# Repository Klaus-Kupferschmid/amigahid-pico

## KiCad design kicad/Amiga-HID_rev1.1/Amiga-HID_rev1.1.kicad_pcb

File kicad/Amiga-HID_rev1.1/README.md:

# Amiga-HID rev1.1 — KiCad Project

> Stand-alone PCB design for the Amiga 2000 HID keyboard adapter.  
> RP235(0/4)A based, 20×55 mm, 4-layer PCB.

## Design Status: ✅ Complete

| Aspect | Status |
|--------|--------|
| Schematic | ✅ Complete (flat design) |
| PCB Layout | ✅ Complete |
| BOM | ✅ JLCPCB-ready |

---

## Bill of Materials (Stand: Mai 2026)

Kanonische BOM-Quelle: [`production/bom.csv`](production/bom.csv)

### MCU & Flash

| Ref | Value | LCSC | Footprint | Usage |
|-----|-------|------|-----------|-------|
| U4 | RP2354_60QFN | C41378174 | QFN-60 7×7mm | MCU (RP2350A mit internem 2MB Flash, alternativ RP2350A pinkompatibel) |
| U3 | W25Q16JVSSIQ | C82317 | SOIC-8 5.3×5.3mm | QSPI Flash 2 MB (DNP bei RP2354A) |
| Y1 | 12MHz | C3003246 | Crystal_SMD_3225 | Systemtakt (18 pF Load) |
| L1 | 3.3µH | C42411119 | L_pol_2016 | RP2350 SMPS-Induktivität (VREG_LX) |

### Power

| Ref | Value | LCSC | Footprint | Usage |
|-----|-------|------|-----------|-------|
| U2 | AMS1117-3.3 | C2688239 | SOT-223 | LDO 5V → 3.3V |
| D1, D2, D3 | PMEG2005AEA | C53114226 | SOD-323 | Power-OR Schottky-Dioden |
| F1 | 500mA | C7202014 | Fuse_1206 | PolyFuse Tastatur-VBUS |
| C1 | 10µF | C15850 | 0805 | VBUS Bulk-Cap |
| C3 | 22µF | C45783 | 0805 | LDO Output Bulk |

### USB & ESD

| Ref | Value | LCSC | Footprint | Usage |
|-----|-------|------|-----------|-------|
| J1 | USB-A | C42614 | USB_A_Edge | USB-A Buchse (Host/Flash) |
| U1 | USBLC6-2SC6 | C19170930 | SOT-23-6 | USB ESD-Schutz |
| R8, R9 | 27Ω | C25100 | 0402 | USB D+/D- Series-Termination |

### Level-Shifter (Amiga Interface)

| Ref | Value | LCSC | Footprint | Usage |
|-----|-------|------|-----------|-------|
| U5 | TXS0102DCUR | C53434 | VSSOP-8 | Bidir 3.3V↔5V für KB_DATA/KB_CLOCK |
| C22 | 100nF | C161530 | 0402 | TXS0102 VccA Decoupling (3V3) |
| C23 | 100nF | C161530 | 0402 | TXS0102 VccB Decoupling (5V) |

### Connectors

| Ref | Value | LCSC | Footprint | Usage |
|-----|-------|------|-----------|-------|
| J2 | JST S5B-XH-A | C42422447 | JST_XH_S5B-XH-A | Amiga / Front Panel (GND, 5V, KBDATA, NC, KBCLK) |
| J3 | Pin Header 1×04 | C52016392 | PinHeader_1x04_P2.54mm | SSD1309 OLED I2C (GND/VCC/SCL/SDA) |
| J4 | Pin Header 1×05 | C225480 | PinHeader_1x05_P2.54mm | Reserve (VSYS/GND/3V3/GP7/GP8) |
| J5 | JST-SH-3 | C160403 | JST_SH_SM03B-SRSS-TB | Pi Debug Probe SWD |
| J6 | JST-SH-3 | C160403 | JST_SH_SM03B-SRSS-TB | Pi Debug Probe UART |
| J7 | Conn_01x06 | C5372829 | PinHeader_1x06_P1.27mm | Zusatz-Reserve-Header |

### LEDs & Switches

| Ref | Value | LCSC | Footprint | Usage |
|-----|-------|------|-----------|-------|
| LED1 | Status_Green | C965804 | LED_0603 | Status/Power LED (GP25) |
| LED2 | Activity_Yellow | C72038 | LED_0603 | Activity LED (GP16) |
| R1, R2 | 1kΩ | C21190 | 0603 | LED-Vorwiderstände |
| SW1 | SW_Push | C139797 | SMD_Tact_4x3 | BOOTSEL Taster |
| SW2 | SW_Push | C139797 | SMD_Tact_4x3 | Reset Taster |

### Capacitors (Decoupling)

| Ref | Value | LCSC | Footprint | Usage |
|-----|-------|------|-----------|-------|
| C2, C4, C5 | 100nF | C1525 | 0402 | LDO Decoupling |
| C6, C7 | 15pF | C18164617 | 0402 | XTAL Load-Caps |
| C8, C9, C10, C12 | 4.7µF | C368809 | 0402 | MCU VREG/1V1 Decoupling |
| C11, C13–C21 | 100nF | C161530 | 0402 | MCU VDD / Flash Decoupling |
| C14 | 100nF | C161530 | 0402 | USB-VBUS Decoupling |

### Resistors

| Ref | Value | LCSC | Footprint | Usage |
|-----|-------|------|-----------|-------|
| R3 | 10kΩ | C25744 | 0402 | QSPI_SS Pullup |
| R4, R6, R7 | 1kΩ | C11702 | 0402 | Pullups |
| R5 | 33Ω | C25105 | 0402 | 3V3 RC-Filter (ADC_AVDD) |
| R10, R11 | 33Ω | C25105 | 0402 | UART TX/RX Series-Termination |
| R12, R13 | DNF | C25900 | 0402 | I2C Pullup-Pads (optional) |

### Misc

| Ref | Value | LCSC | Footprint | Usage |
|-----|-------|------|-----------|-------|
| SJ1 | OLED_VCC_SEL | – | SolderJumper-3 | OLED VCC: Default 3V3, optional 5V |

---

## Power Architecture

Passive dual-source switching (Amiga + PC USB):

```
   Amiga 5V (J2 Pin 2) ──►─D1──►─┬── Board-5V ──► AMS1117-3.3 ──► +3V3
                                 │
   USB-A VBUS (PC) ─────►─D2──►──┤
                                 │
                                 └─D3──►─F1──► USB-A VBUS (Tastatur)
```

✅ No FW logic required · ✅ Brick-resistant · ✅ Crash-safe

---

## GPIO Mapping (REV5)

| GPIO | Function | Connection |
|------|----------|------------|
| GP0 | UART_TX | J6 → Pi Debug Probe RX |
| GP1 | UART_RX | J6 ← Pi Debug Probe TX |
| GP2 | I2C1_SDA | OLED (J3 Pin 4) |
| GP3 | I2C1_SCL | OLED (J3 Pin 3) |
| GP5 | KB_DATA | → TXS0102 → J2 Pin 3 |
| GP6 | KB_CLOCK | → TXS0102 → J2 Pin 5 |
| GP7, GP8 | Reserve | J4 |
| GP16 | LED2 | Activity LED |
| GP25 | LED1 | Status LED |

---

## Tools

- **sync_lcsc_to_sch.py**: Synchronisiert LCSC-Nummern aus `production/bom.csv` in die Schematic

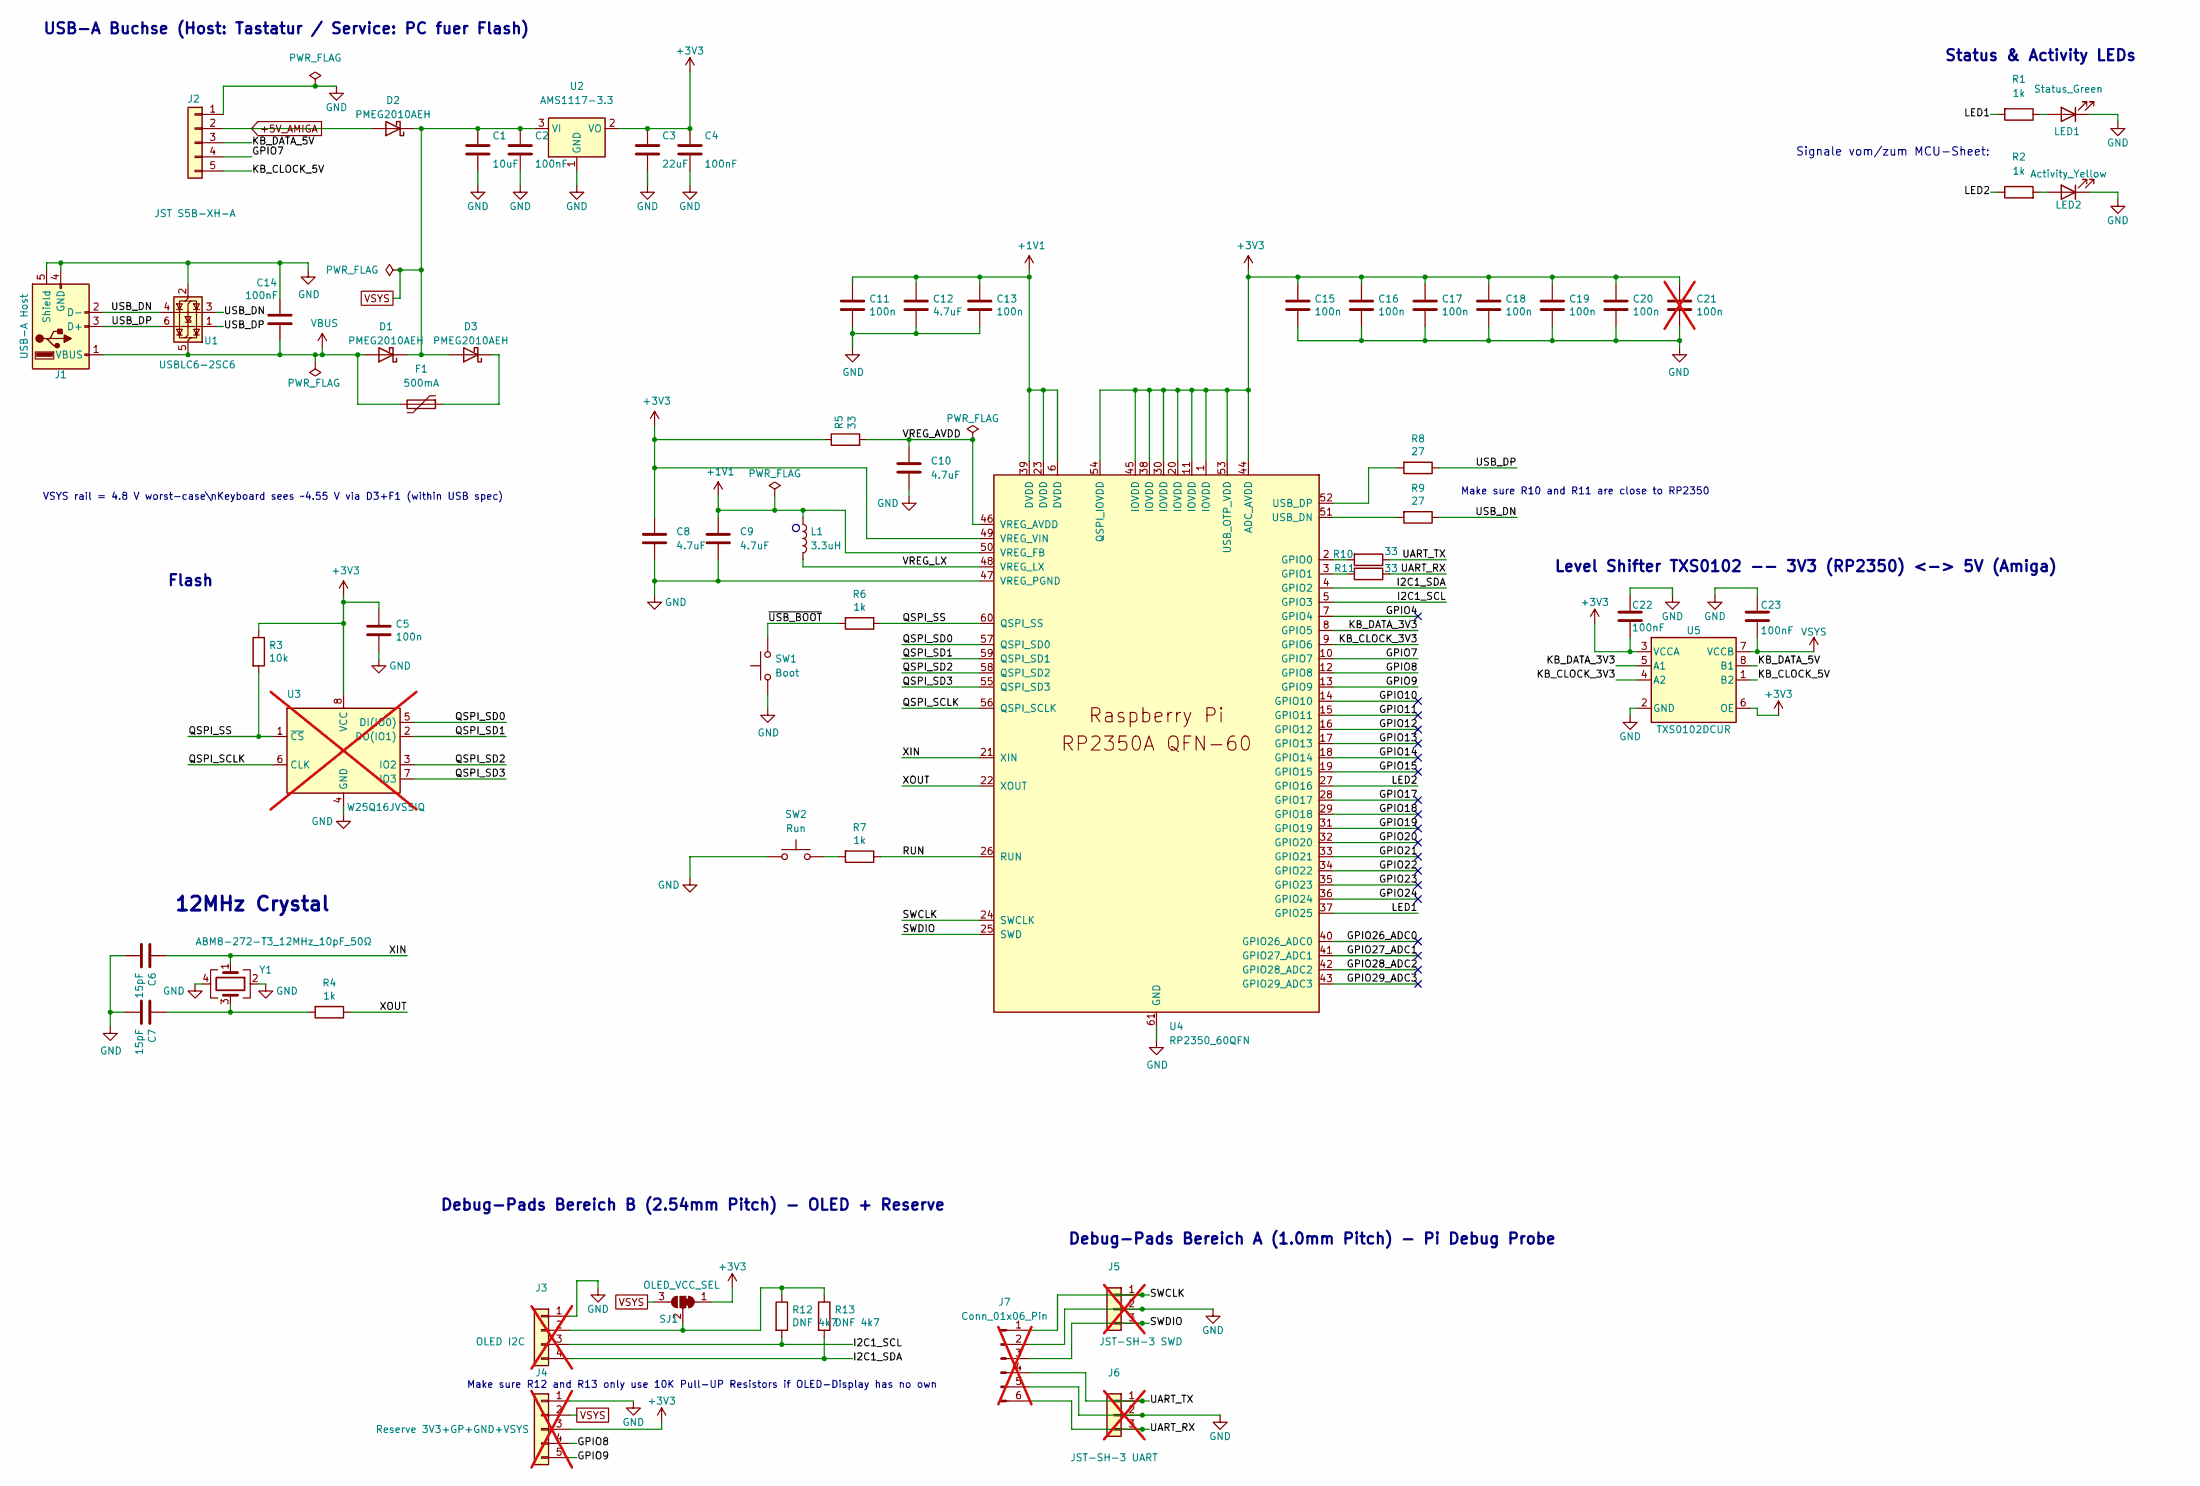
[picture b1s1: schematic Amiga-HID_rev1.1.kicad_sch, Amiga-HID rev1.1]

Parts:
C1: 10uF; C_0805_2012Metric; LCSC C15850
C2, C14, C22, C23: 100nF; C_0402_1005Metric; LCSC C161530
C3: 22uF; C_0805_2012Metric; LCSC C45783
C4: 100nF; C_0402_1005Metric; LCSC C1525
C5: 100n; C_0402_1005Metric; LCSC C1525
C6, C7: 15pF; C_0402_1005Metric; LCSC C18164617
C8, C9, C10, C12: 4.7uF; C_0402_1005Metric; LCSC C368809
C11, C13, C15, C16, C17, C18, C19, C20: 100n; C_0402_1005Metric; LCSC C161530
C21: 100n; C_0402_1005Metric; LCSC C161530; not fitted
D1, D2, D3: PMEG2010AEH; D_SOD-323; LCSC C53114226
F1: 500mA; Fuse_1206_3216Metric; LCSC C7202014
J1: USB-A Host; USB_A_Receptacle_Edge_C42614; LCSC C42614
J2: JST S5B-XH-A; S5B-XH-A; LCSC C42422447
J3: OLED I2C; PinHeader_1x04_P2.54mm_Vertical; LCSC C52016392; not fitted
J4: Reserve 3V3+GP+GND+VSYS; PinHeader_1x05_P2.54mm_Vertical; LCSC C225480; not fitted
J5: JST-SH-3 SWD; JST_SH_SM03B-SRSS-TB_1x03-1MP_P1.00mm_Horizontal; LCSC C160403; not fitted
J6: JST-SH-3 UART; JST_SH_SM03B-SRSS-TB_1x03-1MP_P1.00mm_Horizontal; LCSC C160403; not fitted
J7: Conn_01x06_Pin; PinHeader_1x06_P1.27mm_Vertical; LCSC C5372829; not fitted
L1: 3.3uH; L_pol_2016; MPN MWSA201610H2R2MT; LCSC C42411119
LED1: Status_Green; LED_0603_1608Metric; LCSC C965804
LED2: Activity_Yellow; LED_0603_1608Metric; LCSC C72038
R1, R2: 1k; R_0603_1608Metric; LCSC C21190
R3: 10k; R_0402_1005Metric; LCSC C25744
R4, R6, R7: 1k; R_0402_1005Metric; LCSC C11702
R5, R10, R11: 33; R_0402_1005Metric; LCSC C25105
R8, R9: 27; R_0402_1005Metric; LCSC C25100
R12, R13: DNF 4k7; R_0402_1005Metric; LCSC C25900
SJ1: OLED_VCC_SEL; SolderJumper-3_P1.3mm_Bridged12_RoundedPad1.0x1.5mm
SW1: Boot; SW_Push_1P1T_NO_Vertical_Wuerth_434133025816; LCSC C139797
SW2: Run; SW_Push_1P1T_NO_Vertical_Wuerth_434133025816; LCSC C139797
U1: USBLC6-2SC6; SOT-23-6; LCSC C19170930
U2: AMS1117-3.3; SOT-223-3_TabPin2; LCSC C2688239
U3: W25Q16JVSSIQ; SOIC-8_5.3x5.3mm_P1.27mm; LCSC C82317; not fitted
U4: RP2350_60QFN; RP2350-QFN-60-1EP_7x7_P0.4mm_EP3.4x3.4mm_ThermalVias; LCSC C41378174
U5: TXS0102DCUR; VSSOP-8_2.3x2mm_P0.5mm; LCSC C53434
Y1: ABM8-272-T3_12MHz_10pF_50Ω; Crystal_SMD_3225-4Pin_3.2x2.5mm; LCSC C20625731

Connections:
+1V1: C9.1, C11.1, C12.1, C13.1, L1.1, U4.6 (DVDD), U4.23 (DVDD), U4.39 (DVDD), U4.50 (VREG_FB)
+3V3: C3.1, C4.1, C5.1, C8.1, C15.1, C16.1, C17.1, C18.1, C19.1, C20.1, C21.1, C22.2, J4.3, R3.1, R5.1, SJ1.1 (A), U2.2 (VO), U3.8 (VCC), U4.1 (IOVDD), U4.11 (IOVDD), U4.20 (IOVDD), U4.30 (IOVDD), U4.38 (IOVDD), U4.44 (ADC_AVDD), U4.45 (IOVDD), U4.49 (VREG_VIN), U4.53 (USB_OTP_VDD), U4.54 (QSPI_IOVDD), U5.3 (VCCA), U5.6 (OE)
+5V_AMIGA: D2.2 (A), J2.2
/GPIO4: U4.7 (GPIO4)
/GPIO7: J2.4, U4.10 (GPIO7)
/GPIO8: J4.4, U4.12 (GPIO8)
/GPIO9: J4.5, U4.13 (GPIO9)
/GPIO10: U4.14 (GPIO10)
/GPIO11: U4.15 (GPIO11)
/GPIO12: U4.16 (GPIO12)
/GPIO13: U4.17 (GPIO13)
/GPIO14: U4.18 (GPIO14)
/GPIO15: U4.19 (GPIO15)
/GPIO17: U4.28 (GPIO17)
/GPIO18: U4.29 (GPIO18)
/GPIO19: U4.31 (GPIO19)
/GPIO20: U4.32 (GPIO20)
/GPIO21: U4.33 (GPIO21)
/GPIO22: U4.34 (GPIO22)
/GPIO23: U4.35 (GPIO23)
/GPIO24: U4.36 (GPIO24)
/GPIO26_ADC0: U4.40 (GPIO26_ADC0)
/GPIO27_ADC1: U4.41 (GPIO27_ADC1)
/GPIO28_ADC2: U4.42 (GPIO28_ADC2)
/GPIO29_ADC3: U4.43 (GPIO29_ADC3)
/I2C1_SCL: J3.3, R12.2, U4.5 (GPIO3)
/I2C1_SDA: J3.4, R13.2, U4.4 (GPIO2)
/KB_CLOCK_3V3: U4.9 (GPIO6), U5.4 (A2)
/KB_CLOCK_5V: J2.5, U5.1 (B2)
/KB_DATA_3V3: U4.8 (GPIO5), U5.5 (A1)
/KB_DATA_5V: J2.3, U5.8 (B1)
/LED1: R1.2, U4.37 (GPIO25)
/LED2: R2.1, U4.27 (GPIO16)
/QSPI_SCLK: U3.6 (CLK), U4.56 (QSPI_SCLK)
/QSPI_SD0: U3.5 (DI(IO0)), U4.57 (QSPI_SD0)
/QSPI_SD1: U3.2 (DO(IO1)), U4.59 (QSPI_SD1)
/QSPI_SD2: U3.3 (IO2), U4.58 (QSPI_SD2)
/QSPI_SD3: U3.7 (IO3), U4.55 (QSPI_SD3)
/QSPI_SS: R3.2, R6.1, U3.1 (~CS), U4.60 (QSPI_SS)
/RUN: R7.1, U4.26 (RUN)
/SWCLK: J5.1, J7.1, U4.24 (SWCLK)
/SWDIO: J5.3, J7.3, U4.25 (SWD)
/UART_RX: J6.3, J7.6, R11.1
/UART_TX: J6.1, J7.4, R10.1
/USB_DN: J1.2 (D-), R9.1, U1.3 (I/O2), U1.4 (I/O2)
/USB_DP: J1.3 (D+), R8.1, U1.1 (I/O1), U1.6 (I/O1)
/VREG_AVDD: C10.1, R5.2, U4.46 (VREG_AVDD)
/VREG_LX: L1.2, U4.48 (VREG_LX)
/XIN: C6.1, U4.21 (XIN), Y1.1
/XOUT: R4.1, U4.22 (XOUT)
/~USB_BOOT: R6.2, SW1.2
GND: C1.2, C2.2, C3.2, C4.2, C5.2, C6.2, C7.2, C8.2, C9.2, C10.2, C11.2, C12.2, C13.2, C14.1, C15.2, C16.2, C17.2, C18.2, C19.2, C20.2, C21.2, C22.1, C23.1, J1.4 (GND), J1.5 (Shield), J2.1, J3.1, J4.1, J5.2, J6.2, J7.2, J7.5, LED1.1 (K), LED2.1 (K), SW1.1, SW2.1, U1.2 (GND), U2.1 (GND), U3.4 (GND), U4.47 (VREG_PGND), U4.61 (GND), U5.2 (GND), Y1.2, Y1.4
unnamed: C7.1, R4.2, Y1.3
unnamed: D3.1 (K), F1.1
unnamed: J3.2, R12.1, R13.1, SJ1.2 (C)
unnamed: LED1.2 (A), R1.1
unnamed: LED2.2 (A), R2.2
unnamed: R7.2, SW2.2
unnamed: R10.2, U4.2 (GPIO0)
unnamed: R11.2, U4.3 (GPIO1)
unnamed: R9.2, U4.51 (USB_DN)
unnamed: R8.2, U4.52 (USB_DP)
VBUS: C14.2, D1.2 (A), F1.2, J1.1 (VBUS), U1.5 (VBUS)
VSYS: C1.1, C2.1, C23.2, D1.1 (K), D2.1 (K), D3.2 (A), J4.2, SJ1.3 (B), U2.3 (VI), U5.7 (VCCB)

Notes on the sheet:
USB-A Buchse (Host: Tastatur / Service: PC fuer Flash)
Make sure R12 and R13 only use 10K Pull-UP Resistors if OLED-Display has no own
Signale vom/zum MCU-Sheet:
Status & Activity LEDs
Flash
Debug-Pads Bereich B (2.54mm Pitch) - OLED + Reserve
Make sure R10 and R11 are close to RP2350
Level Shifter TXS0102 -- 3V3 (RP2350) <-> 5V (Amiga)
12MHz Crystal
VSYS rail = 4.8 V worst-case\nKeyboard sees ~4.55 V via D3+F1 (within USB spec)
Debug-Pads Bereich A (1.0mm Pitch) - Pi Debug Probe

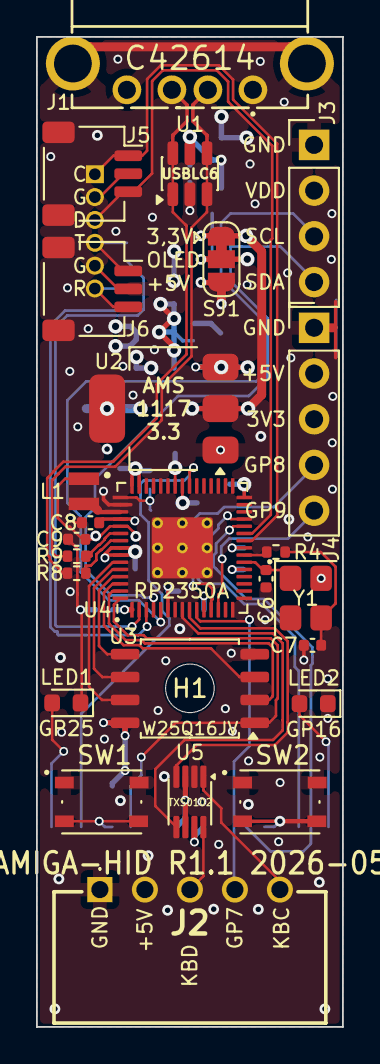
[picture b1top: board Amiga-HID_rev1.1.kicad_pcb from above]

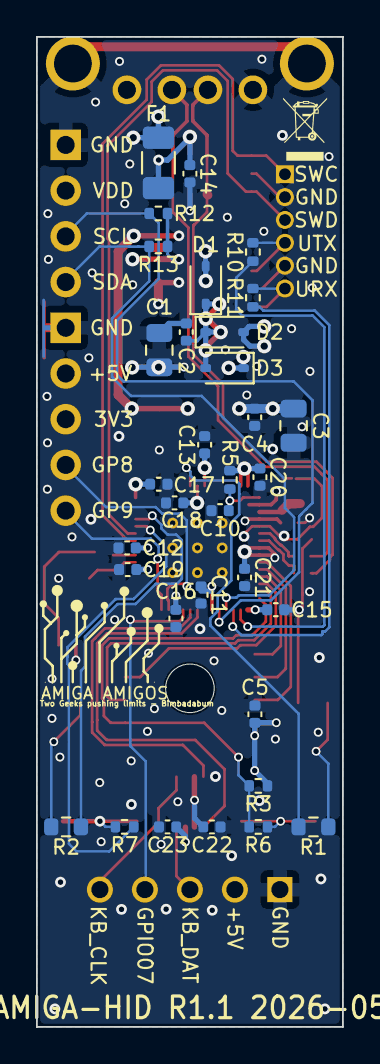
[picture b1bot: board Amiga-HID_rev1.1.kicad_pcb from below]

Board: 4 copper layers, 17.0 x 55.0 mm, 60 parts (33 on the bottom side), 45 nets.

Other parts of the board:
H1: MountingHole; MountingHole_2.7mm

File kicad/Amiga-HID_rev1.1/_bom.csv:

"Designator","Comment","Footprint","JLCPCB Part #","Usage"
"C1","10uF","Capacitor_SMD:C_0805_2012Metric","C15850","VBUS / Board-5V Bulk-Cap"
"C2","100nF","Capacitor_SMD:C_0402_1005Metric","C161530","LDO U2 IN-Decoupling"
"C3","22uF","Capacitor_SMD:C_0805_2012Metric","C45783","LDO U2 OUT Bulk (3V3)"
"C4","100nF","Capacitor_SMD:C_0402_1005Metric","C1525","LDO U2 OUT-Decoupling"
"C5","100nF","Capacitor_SMD:C_0402_1005Metric","C1525","Decoupling"
"C6","15pF","Capacitor_SMD:C_0402_1005Metric","C18164617","XTAL Y1 Load-Cap"
"C7","15pF","Capacitor_SMD:C_0402_1005Metric","C18164617","XTAL Y1 Load-Cap"
"C8","4.7uF","Capacitor_SMD:C_0402_1005Metric","C368809","MCU VREG_VIN Decoupling"
"C9","4.7uF","Capacitor_SMD:C_0402_1005Metric","C368809","MCU VREG SMPS-Cap"
"C10","4.7uF","Capacitor_SMD:C_0402_1005Metric","C368809","MCU 1V1 Bulk"
"C11","100nF","Capacitor_SMD:C_0402_1005Metric","C161530","3V3 RC-Filter mit R5 (ADC/USB_VDD)"
"C12","4.7uF","Capacitor_SMD:C_0402_1005Metric","C368809","MCU 1V1 Bulk"
"C13","100nF","Capacitor_SMD:C_0402_1005Metric","C161530","Decoupling"
"C14","100nF","Capacitor_SMD:C_0402_1005Metric","C161530","USB-VBUS Decoupling am Power-OR (USBLC6 / Schottky-Knoten)"
"C15","100nF","Capacitor_SMD:C_0402_1005Metric","C161530","MCU VDD Pin-Decoupling"
"C16","100nF","Capacitor_SMD:C_0402_1005Metric","C161530","MCU VDD Pin-Decoupling"
"C17","100nF","Capacitor_SMD:C_0402_1005Metric","C161530","MCU VDD Pin-Decoupling"
"C18","100nF","Capacitor_SMD:C_0402_1005Metric","C161530","MCU VDD Pin-Decoupling"
"C19","100nF","Capacitor_SMD:C_0402_1005Metric","C161530","MCU VDD Pin-Decoupling"
"C20","100nF","Capacitor_SMD:C_0402_1005Metric","C161530","MCU VDD Pin-Decoupling"
"C21","100nF","Capacitor_SMD:C_0402_1005Metric","C161530","U3 Flash VCC Decoupling (DNP bei RP2354A)"
"C22","100nF","Capacitor_SMD:C_0402_1005Metric","C161530","TXS0102 U5 Vcc-A Decoupling (3V3)"
"C23","100nF","Capacitor_SMD:C_0402_1005Metric","C161530","TXS0102 U5 Vcc-B Decoupling (5V)"
"D1","PMEG2005AEA 115-JSM","Diode_SMD:D_SOD-323","C53114226","Power-OR: Amiga 5V (J2 Pin2) -> Board-5V"
"D2","PMEG2005AEA 115-JSM","Diode_SMD:D_SOD-323","C53114226","Power-OR: USB-A VBUS (PC-Speisung) -> Board-5V"
"D3","PMEG2005AEA 115-JSM","Diode_SMD:D_SOD-323","C53114226","Power-OR: Board-5V -> USB-A VBUS (Tastatur-Speisung)"
"F1","500mA","Fuse:Fuse_1206_3216Metric","C7202014","PolyFuse Tastatur-VBUS (Kurzschluss-Schutz)"
"J1","USB-A Host","Amiga-HID_rev1.0:USB_A_Receptacle_Edge_C42614","C42614","USB-A Buchse (Tastatur-Host / PC-Flash via USB-A<->USB-A)"
"J2","JST-XH-5A","Connector_JST:JST_XH_B5B-XH-A_1x05_P2.50mm_Vertical","C7551124","Verbindung Amiga / Front Panel (GND, 5V, KBDATA, NC, KBCLK)"
"J3","OLED I2C","Connector_PinHeader_2.54mm:PinHeader_1x04_P2.54mm_Vertical","C52016392","SSD1309 OLED I2C (GND/VCC/SCL/SDA)"
"J4","Reserve 3V3+GP+GND+VSYS","Connector_PinHeader_2.54mm:PinHeader_1x05_P2.54mm_Vertical","C225480","Reserve 5-Pin (VSYS/GND/3V3/GP7/GP8)"
"J5","JST-SH-3 SWD","Connector_JST:JST_SH_SM03B-SRSS-TB_1x03-1MP_P1.00mm_Horizontal","C160403","Pi Debug Probe SWD (SWCLK/GND/SWDIO)"
"J6","JST-SH-3 UART","Connector_JST:JST_SH_SM03B-SRSS-TB_1x03-1MP_P1.00mm_Horizontal","C160403","Pi Debug Probe UART (TX/GND/RX)"
"J7","Conn_01x06_Pin","Connector_PinHeader_1.27mm:PinHeader_1x06_P1.27mm_Vertical","C5372829","Zusatz-Header (Reserve)"
"L1","3.3uH","Amiga-HID_rev1.0:L_pol_2016","C42411119","RP2350 SMPS-Induktivitaet (VREG_LX), Abracon AOTA-B201610S3R3 shielded power inductor"
"LED1","Status_Green","LED_SMD:LED_0603_1608Metric","C965804","Status/Power LED an GP25"
"LED2","Activity_Yellow","LED_SMD:LED_0603_1608Metric","C72038","Activity LED (USB-Traffic) an GP16"
"R1","330","Resistor_SMD:R_0603_1608Metric","C23138","LED1 Vorwiderstand (GP25 -> Status_Green)"
"R2","330","Resistor_SMD:R_0603_1608Metric","C23138","LED2 Vorwiderstand (GP16 -> Activity_Yellow)"
"R3","10k","Resistor_SMD:R_0402_1005Metric","C25744","QSPI_SS Pullup gegen +3V3 (Pico-2-Ref Pflicht)"
"R4","1k","Resistor_SMD:R_0402_1005Metric","C11702","Pullup / generischer Widerstand"
"R5","33","Resistor_SMD:R_0402_1005Metric","C25105","3V3 RC-Filter mit C11 (ADC_AVDD / USB_VDD33)"
"R6","1k","Resistor_SMD:R_0402_1005Metric","C11702","Pullup / generischer Widerstand"
"R7","1k","Resistor_SMD:R_0402_1005Metric","C11702","Pullup / generischer Widerstand"
"R8","27","Resistor_SMD:R_0402_1005Metric","C25100","USB D+ Series-Termination (USB-Spec 90 Ohm diff)"
"R9","27","Resistor_SMD:R_0402_1005Metric","C25100","USB D- Series-Termination (USB-Spec 90 Ohm diff)"
"R10","33","Resistor_SMD:R_0402_1005Metric","C25105","UART_TX Series-Termination MCU GP0 -> J6 Pin1"
"R11","33","Resistor_SMD:R_0402_1005Metric","C25105","UART_RX Series-Termination J6 Pin3 -> MCU GP1"
"R12","DNF","Resistor_SMD:R_0402_1005Metric","C25900","I2C1_SDA Pullup-Pad (DNF, OLED-Modul hat eigene Pullups; bei Bedarf 4k7)"
"R13","DNF","Resistor_SMD:R_0402_1005Metric","C25900","I2C1_SCL Pullup-Pad (DNF, OLED-Modul hat eigene Pullups; bei Bedarf 4k7)"
"SJ1","OLED_VCC_SEL","Jumper:SolderJumper-3_P1.3mm_Bridged12_RoundedPad1.0x1.5mm",,"Loetjumper OLED VCC: Default 3V3 (Pads 1+2 gebrueckt), alternativ auf 5V umloeten"
"SW1","SW_Push","Amiga-HID_rev1.0:SW_SMD_Tact_4x3_4P_C139797","C139797","BOOTSEL Hardware-Fallback Taster"
"SW2","SW_Push","Amiga-HID_rev1.0:SW_SMD_Tact_4x3_4P_C139797","C139797","Reset / User-Taster"
"U1","USBLC6-2SC6","Package_TO_SOT_SMD:SOT-23-6","C19170930","USB ESD-Schutz auf D+/D-"
"U2","AMS1117-3.3","Package_TO_SOT_SMD:SOT-223-3_TabPin2","C2688239","LDO 5V -> 3V3 (>=800 mA)"
"U3","W25Q16JVSSIQ","Amiga-HID_rev1.0:SOIC-8_5.3x5.3mm_P1.27mm","C82317","QSPI Flash 2 MB (DNP bei RP2354A flashless)"
"U4","RP2354_60QFN","Amiga-HID_rev1.0:RP2350-QFN-60-1EP_7x7_P0.4mm_EP3.4x3.4mm_ThermalVias","C41378174","MCU RP2350A (alternativ pinkompatibel RP2354A mit internem Stacked-Flash)"
"U5","TXS0102DCUR","Package_SO:VSSOP-8_2.3x2mm_P0.5mm","C53434","Bidir Level-Shifter 3V3<->5V fuer KB_DATA/KB_CLOCK"
"Y1","ABM8-272-T3_12MHz_10pF","Crystal:Crystal_SMD_3225-4Pin_3.2x2.5mm","C20625731","Systemtakt 12 MHz (Abracon ABM8-272-T3, Raspberry Pi zertifiziert)"

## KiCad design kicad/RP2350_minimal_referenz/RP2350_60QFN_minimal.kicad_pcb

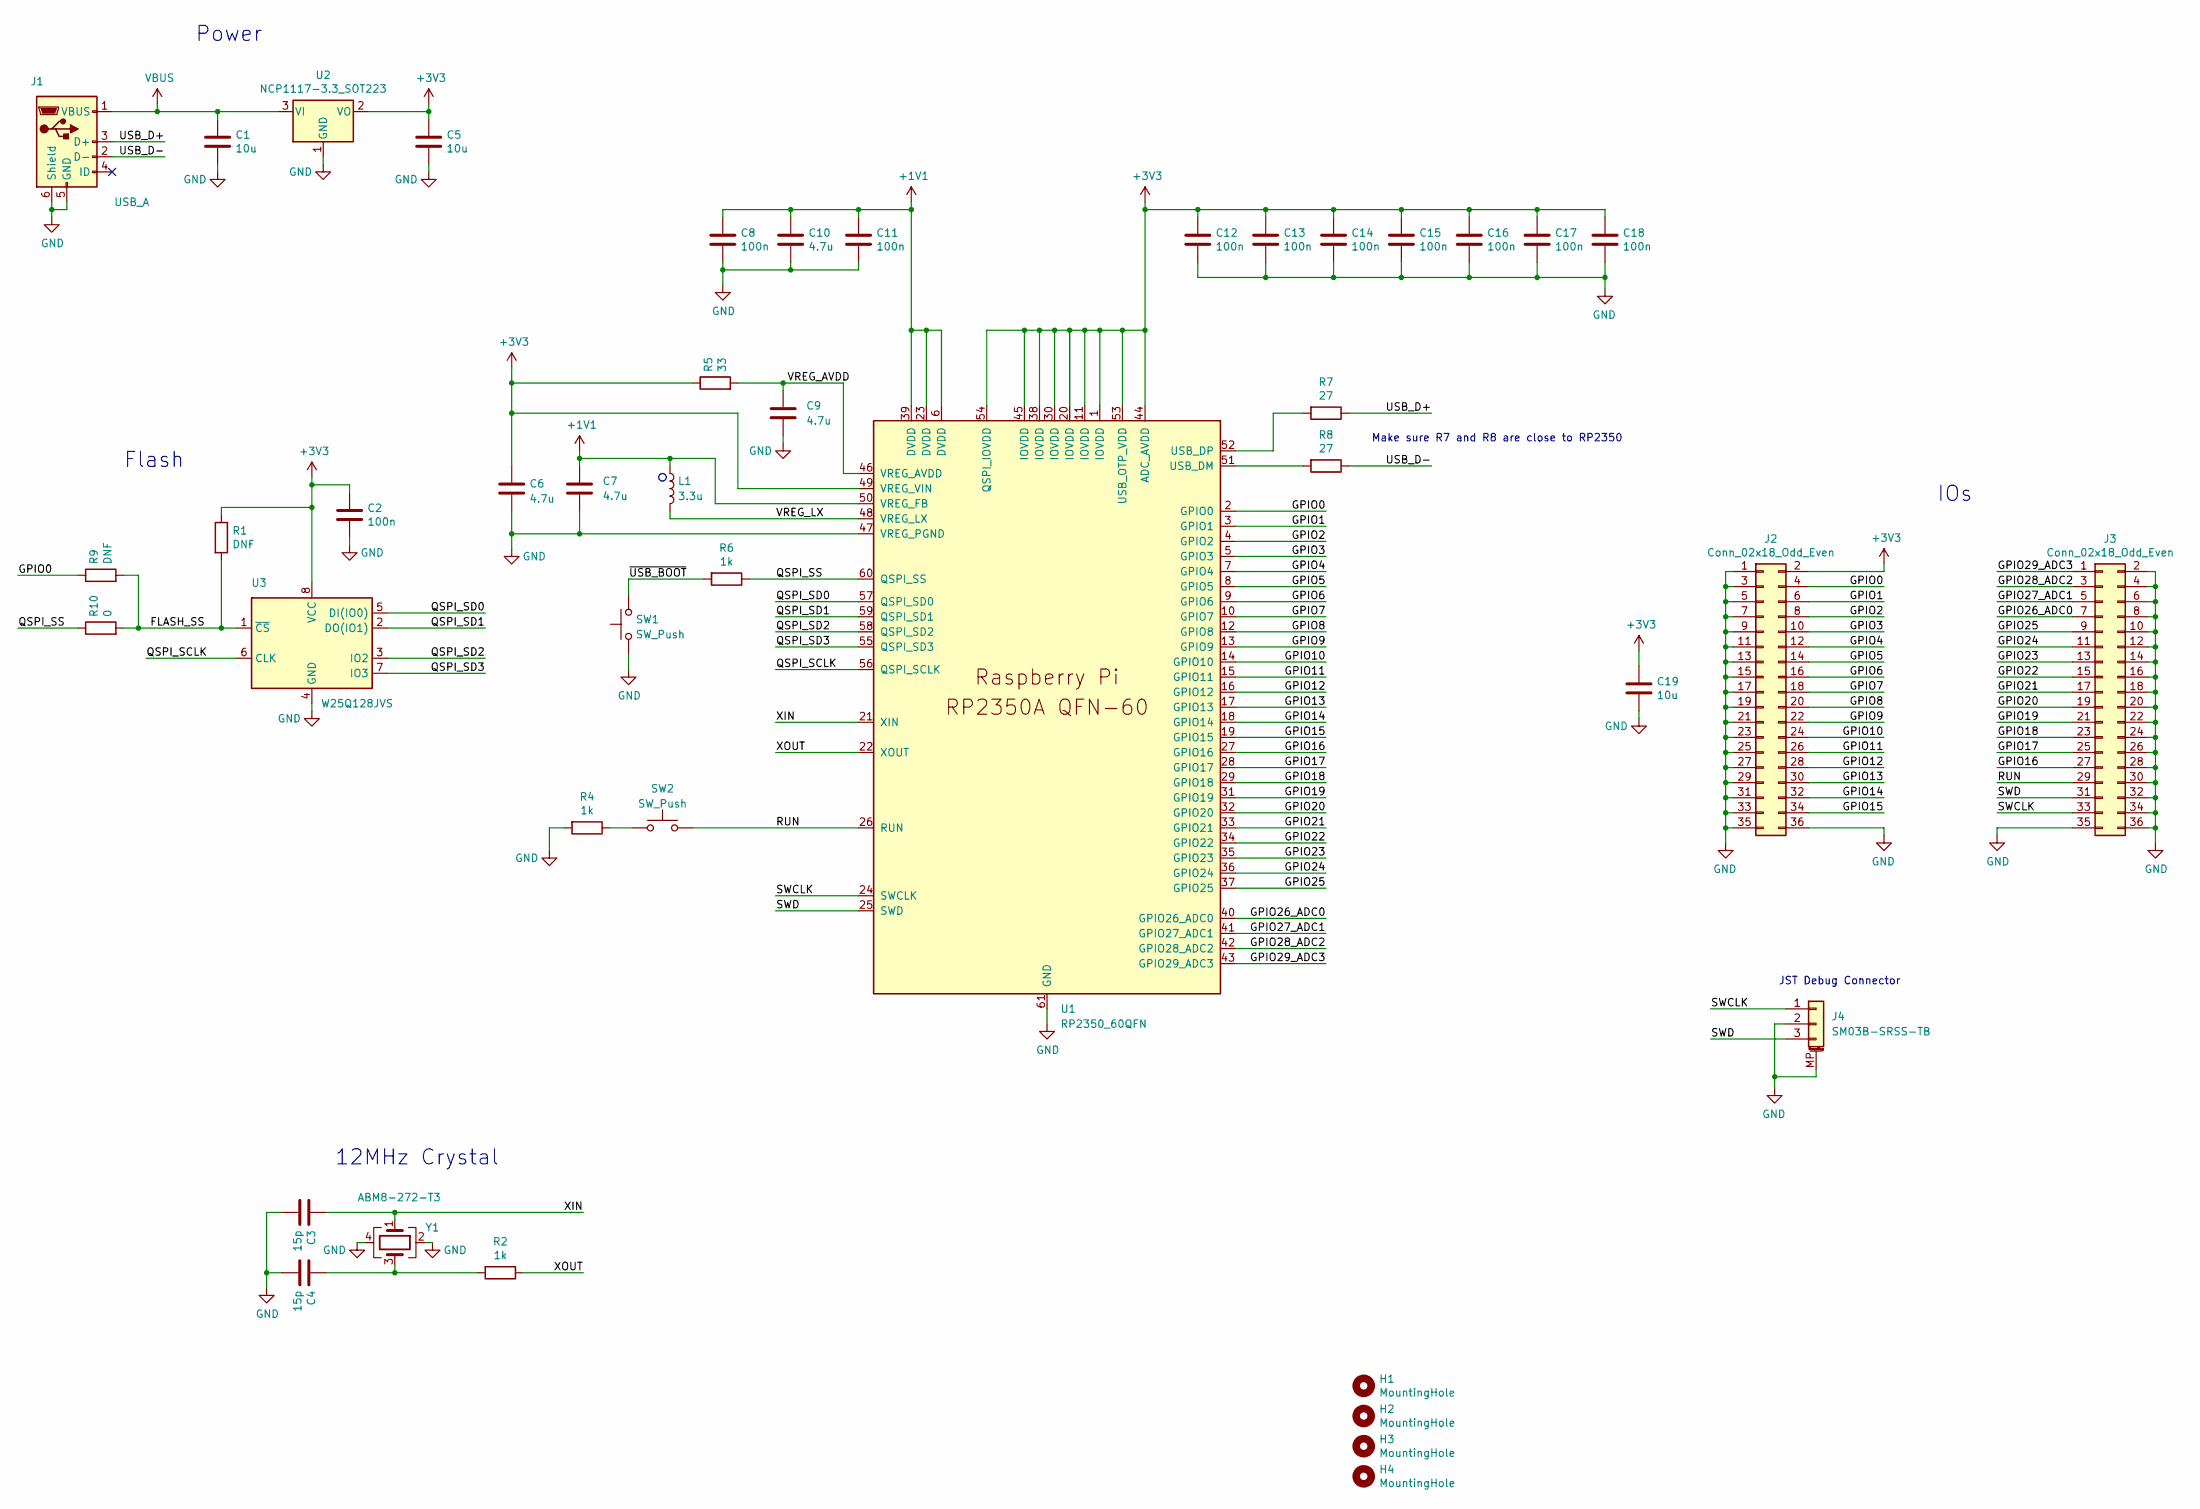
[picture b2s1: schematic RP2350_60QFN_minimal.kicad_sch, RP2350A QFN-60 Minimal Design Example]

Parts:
C1, C5, C19: 10u; C_0805_2012Metric
C2, C8, C11, C12, C13, C14, C15, C16, C17, C18: 100n; C_0402_1005Metric
C3, C4: 15p; C_0402_1005Metric
C6, C7: 4.7u; C_0402_1005Metric_small_pads
C9, C10: 4.7u; C_0402_1005Metric
H1, H2, H3, H4: MountingHole; MountingHole_2.7mm_M2.5
J1: USB_A; USB_Micro-B_Amphenol_10103594-0001LF_Horizontal
J2, J3: Conn_02x18_Odd_Even; PinHeader_2x18_P2.54mm_Vertical
J4: SM03B-SRSS-TB; JST_SH_SM03B-SRSS-TB_1x03-1MP_P1.00mm_Horizontal
L1: 3.3u; L_pol_2016
R1, R9: DNF; R_0402_1005Metric
R2, R4, R6: 1k; R_0402_1005Metric
R5: 33; R_0402_1005Metric
R7, R8: 27; R_0402_1005Metric
R10: 0; R_0402_1005Metric
SW1, SW2: SW_Push; SW_Push_1P1T_NO_Vertical_Wuerth_434133025816
U1: RP2350_60QFN; RP2350-QFN-60-1EP_7x7_P0.4mm_EP3.4x3.4mm_ThermalVias
U2: NCP1117-3.3_SOT223; SOT-223-3_TabPin2
U3: W25Q128JVS; SOIC-8_5.23x5.23mm_P1.27mm
Y1: ABM8-272-T3; Crystal_SMD_3225-4Pin_3.2x2.5mm

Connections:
+1V1: C7.1, C8.1, C10.1, C11.1, L1.1, U1.6 (DVDD), U1.23 (DVDD), U1.39 (DVDD), U1.50 (VREG_FB)
+3V3: C2.1, C5.1, C6.1, C12.1, C13.1, C14.1, C15.1, C16.1, C17.1, C18.1, C19.1, J2.2, R1.1, R5.1, U1.1 (IOVDD), U1.11 (IOVDD), U1.20 (IOVDD), U1.30 (IOVDD), U1.38 (IOVDD), U1.44 (ADC_AVDD), U1.45 (IOVDD), U1.49 (VREG_VIN), U1.53 (USB_OTP_VDD), U1.54 (QSPI_IOVDD), U2.2 (VO), U3.8 (VCC)
/FLASH_SS: R1.2, R9.2, R10.2, U3.1 (~CS)
/GPIO0: J2.4, R9.1, U1.2 (GPIO0)
/GPIO1: J2.6, U1.3 (GPIO1)
/GPIO2: J2.8, U1.4 (GPIO2)
/GPIO3: J2.10, U1.5 (GPIO3)
/GPIO4: J2.12, U1.7 (GPIO4)
/GPIO5: J2.14, U1.8 (GPIO5)
/GPIO6: J2.16, U1.9 (GPIO6)
/GPIO7: J2.18, U1.10 (GPIO7)
/GPIO8: J2.20, U1.12 (GPIO8)
/GPIO9: J2.22, U1.13 (GPIO9)
/GPIO10: J2.24, U1.14 (GPIO10)
/GPIO11: J2.26, U1.15 (GPIO11)
/GPIO12: J2.28, U1.16 (GPIO12)
/GPIO13: J2.30, U1.17 (GPIO13)
/GPIO14: J2.32, U1.18 (GPIO14)
/GPIO15: J2.34, U1.19 (GPIO15)
/GPIO16: J3.27, U1.27 (GPIO16)
/GPIO17: J3.25, U1.28 (GPIO17)
/GPIO18: J3.23, U1.29 (GPIO18)
/GPIO19: J3.21, U1.31 (GPIO19)
/GPIO20: J3.19, U1.32 (GPIO20)
/GPIO21: J3.17, U1.33 (GPIO21)
/GPIO22: J3.15, U1.34 (GPIO22)
/GPIO23: J3.13, U1.35 (GPIO23)
/GPIO24: J3.11, U1.36 (GPIO24)
/GPIO25: J3.9, U1.37 (GPIO25)
/GPIO26_ADC0: J3.7, U1.40 (GPIO26_ADC0)
/GPIO27_ADC1: J3.5, U1.41 (GPIO27_ADC1)
/GPIO28_ADC2: J3.3, U1.42 (GPIO28_ADC2)
/GPIO29_ADC3: J3.1, U1.43 (GPIO29_ADC3)
/QSPI_SCLK: U1.56 (QSPI_SCLK), U3.6 (CLK)
/QSPI_SD0: U1.57 (QSPI_SD0), U3.5 (DI(IO0))
/QSPI_SD1: U1.59 (QSPI_SD1), U3.2 (DO(IO1))
/QSPI_SD2: U1.58 (QSPI_SD2), U3.3 (IO2)
/QSPI_SD3: U1.55 (QSPI_SD3), U3.7 (IO3)
/QSPI_SS: R6.1, R10.1, U1.60 (QSPI_SS)
/RUN: J3.29, SW2.2, U1.26 (RUN)
/SWCLK: J3.33, J4.1, U1.24 (SWCLK)
/SWD: J3.31, J4.3, U1.25 (SWD)
/USB_D+: J1.3 (D+), R7.1
/USB_D-: J1.2 (D-), R8.1
/VREG_AVDD: C9.1, R5.2, U1.46 (VREG_AVDD)
/VREG_LX: L1.2, U1.48 (VREG_LX)
/XIN: C3.1, U1.21 (XIN), Y1.1
/XOUT: R2.1, U1.22 (XOUT)
/~USB_BOOT: R6.2, SW1.2
GND: C1.2, C2.2, C3.2, C4.2, C5.2, C6.2, C7.2, C8.2, C9.2, C10.2, C11.2, C12.2, C13.2, C14.2, C15.2, C16.2, C17.2, C18.2, C19.2, J1.5 (GND), J1.6 (Shield), J2.1, J2.3, J2.5, J2.7, J2.9, J2.11, J2.13, J2.15, J2.17, J2.19, J2.21, J2.23, J2.25, J2.27, J2.29, J2.31, J2.33, J2.35, J2.36, J3.2, J3.4, J3.6, J3.8, J3.10, J3.12, J3.14, J3.16, J3.18, J3.20, J3.22, J3.24, J3.26, J3.28, J3.30, J3.32, J3.34, J3.35, J3.36, J4.2, J4.MP (MountPin), R4.2, SW1.1, U1.47 (VREG_PGND), U1.61 (GND), U2.1 (GND), U3.4 (GND), Y1.2, Y1.4
unnamed: C4.1, R2.2, Y1.3
unnamed: R4.1, SW2.1
unnamed: R8.2, U1.51 (USB_DM)
unnamed: R7.2, U1.52 (USB_DP)
VBUS: C1.1, J1.1 (VBUS), U2.3 (VI)

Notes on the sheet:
JST Debug Connector
IOs
Flash
Make sure R7 and R8 are close to RP2350
12MHz Crystal
Power

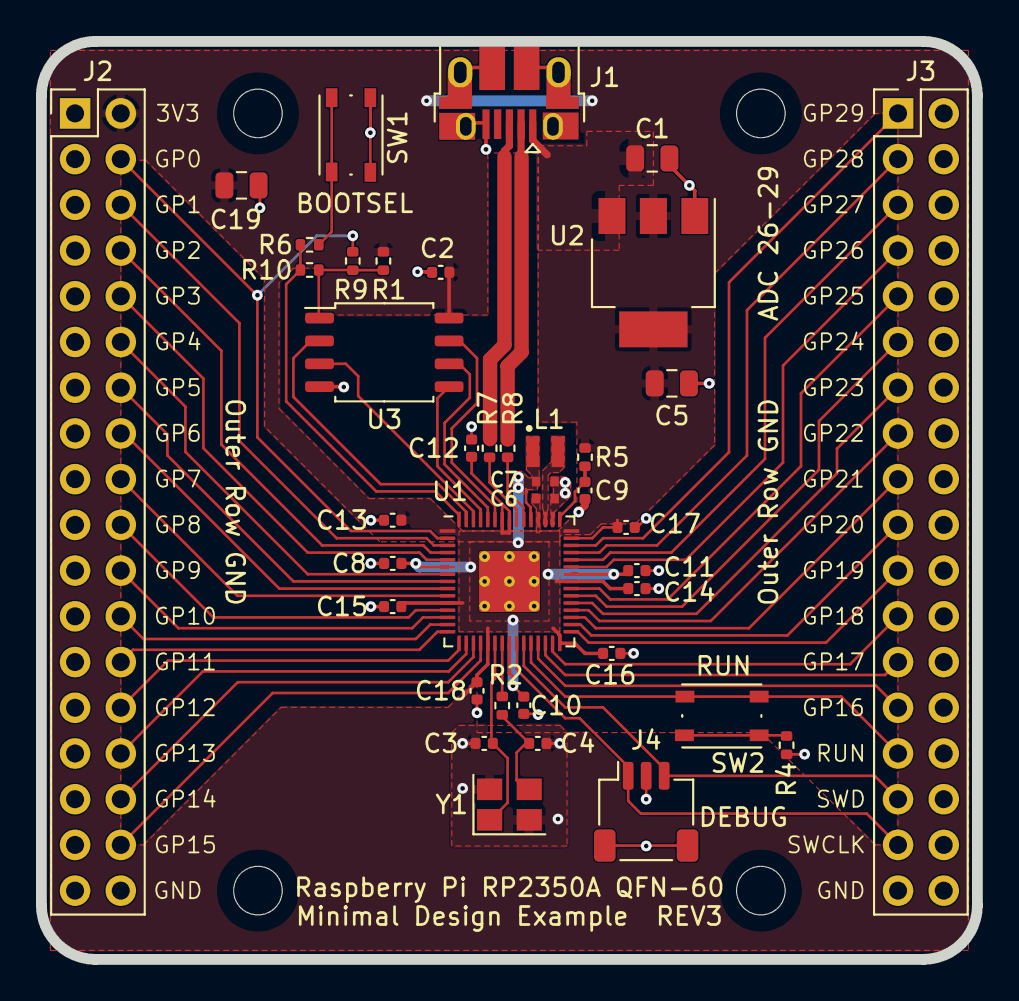
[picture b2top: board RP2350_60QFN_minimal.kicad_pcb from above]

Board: 2 copper layers, 52.0 x 51.0 mm, 43 parts (0 on the bottom side), 55 nets.

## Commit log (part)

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2026-04-29 Add local development environment for RP2350/Pico2 debugging
    - VSCode launch configs for probe-rs debugger
    - Build scripts (release + debug) for Windows/MSVC
    - Flash scripts for UF2 and probe-rs
    - Upstream sync scripts for tracking borb/amigahid-pico
    - Documentation for breadboard test setup
    - Copilot instructions for project context
2026-04-29 Add upstream sync documentation
2026-05-02 1. vollständiger schematic entwurf
2026-05-02 One Top-Level Schematic
2026-05-02 Inspection 0 Warnings
2026-05-02 Footprints sind vollständig
2026-05-03 korrekte USB-A Buchse
2026-05-03 Add pyOCD and additional debug configurations
2026-05-03 alle 3d modelle implementiert
2026-05-04 pico referenz design
2026-05-04 aufteilung Bauteile Vorder und Rückseite
2026-05-04 Wiederstände überarbeitet
2026-05-04 bom überarbeitet
2026-05-06 Anordnung der Bauteile abgeschlossen
2026-05-08 fast fertig mit routing
2026-05-08 Amig-HID_Rev1 Inspector 0 Errors
2026-05-08 J6 war spiegelverkehrt
2026-05-11 layou Fehler behoben
2026-05-13 BOm aktualisiert
2026-05-13 nicht bestückte Komponenten entfernt aus 3d-Ansicht
2026-06-02 test led Code erstellt Software erfolgreich getestet
